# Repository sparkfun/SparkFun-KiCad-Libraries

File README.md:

SparkFun Electronics KiCad Libraries
====================================

This repository contains the SparkFun KiCad Libraries of commonly used parts. It is a cultivated combination of KiCad stock parts,  SparkFun-unique footprints, and open-source 3D models. The main branch is generally proven out but we apologize in advance if these libraries have errors. Please report any issues! We'll fix them quickly.

**Note:** The SparkFun KiCad components contain internal part numbers (**PROD_ID-\***) for ease of manufacture for the SparkFun SMD lines. 

## Theory

KiCad is very good and has a large number of industry specified symbols and footprints. SparkFun has a large number of unique parts and components created since 2002. Rather than converting all previous [SparkFun Eagle libraries](https://github.com/sparkfun/SparkFun-Eagle-Libraries) to KiCad, we are adding new parts to these libraries as we need them for new projects. This gives us the opportunity to clear out old badness, but opens the door to new badness (ie, incorrect footprints) so reader beware!

The SparkFun approach: when a new part needs to be added we decide whether to use a KiCad stock symbol, edit it for use, or create it from scratch. We give preference to the stock KiCad symbol. We give heavy preference to using the original SparkFun footprint, but look at the stock KiCad footprint for inspiration as well. We try to follow the [KiCad Library Conventions](https://klc.kicad.org/) where it makes sense.

Additionally, SparkFun needs to assign various unique manufacturing data (ie, internal part numbers) to parts. To alleviate this, there is a large number of components with an identical symbol each with their own production ID information. For example, capacitors:

We use the following naming conventions to create our 'bubble gum' parts: 

* [capacity]\_[size]\_[voltage]_[tolerance]
* [resistance]\_[size]\_[wattage optional]_[tolerance optional]
* [inductance]\_[size]\_[max current]
* [led color]\_[size]\_[wavelength optional]

## Installing and using these libraries

* [Installing a release via the KiCad PCM](#installing-a-release-via-the-kicad-pcm)
* [Installing a release from zip file - without the PCM_ Library nickname prefix](#installing-a-release-from-zip-file---without-the-pcm_-library-nickname-prefix)
* [Download the current libraries as a zip file](#download-the-current-libraries-as-a-zip-file)
* [Using Git](#using-git)

Internally, these libraries use an Environmental Variable named `SPARKFUN_KICAD_LIBRARY` to reference the footprints and 3D models. This is converted into `KICAD9_3RD_PARTY` during the release process. The release zip file Assets contain `KICAD9_3RD_PARTY` paths. At SparkFun, we use the library as-is with the original `SPARKFUN_KICAD_LIBRARY` environmental variable paths. Our open-source KiCad designs will contain those same environmental variable paths. If you want to be able to _edit_ existing SparkFun schematics and board designs directly, rather than just make use of our components, you need to manually install a true copy or clone of the library. See [Download the current libraries as a zip file](#download-the-current-libraries-as-a-zip-file) and [Using Git](#using-git) below.

### Installing a release via the KiCad PCM

From the fall of 2025, releases of these libraries are available via the KiCad Plugin and Content Manager (PCM).

Open the PCM, select the "Libraries" tab, and type "SparkFun" into the search box. The "Install" button will install the latest release of the libraries.

**If you are using KiCad 10 :** after installing the libraries through the PCM, **close KiCad** and reopen. Only then will the new libraries be visible.

**Note:** this method assumes you have the KiCad Library nickname prefix set to the default of 'PCM_'. If you have cleared the Library nickname prefix, use the [next option](#installing-a-release-from-zip-file---without-the-pcm_-library-nickname-prefix) to install from zip file.

### Installing a release from zip file - without the PCM_ Library nickname prefix

In the KiCad Preferences, you will find settings for "Packages and Updates". The "Library nickname prefix" is applied to any libraries installed through the Plugin and Content Manager (PCM).

If you install these libraries though the PCM, the installation assumes the prefix is 'PCM_'. The symbol footprint names will all be prefixed with 'PCM_'. If you have cleared the prefix, you will need to manually install a different version of the libraries without the footprint prefix:

* Navigate to the libraries [Releases page](https://github.com/sparkfun/SparkFun-KiCad-Libraries/releases)
* You will find two zip file "Assets" attached to each release
* Download the **"without-pcm"** zip file
* In the PCM, use the "Install from File..." option to install the zip file

**If you are using KiCad 10 :** after installing the libraries from file, **close KiCad** and reopen. Only then will the new libraries be visible.

If you are changing the Library prefix to use this installation method, we recommend: clearing the prefix, OK the changes, **close KiCad** and reopen before installing the zip file.

### Download the current libraries as a zip file

Instead of waiting for a release, you can download a copy of the libraries at any time by clicking on the big green `<> Code` button above and selecting the `Download ZIP` option. Or, click on the icon below:

Unzip the file somewhere convenient, usually in `Documents`. If needed, change the folder name from `SparkFun-KiCad-Libraries-main` to `SparkFun-KiCad-Libraries`. Open the KiCad **Symbol Editor** and select `Preferences \ Configure Paths`. Add a new Environmental Variable called `SPARKFUN_KICAD_LIBRARY` and set the Path to the `SparkFun-KiCad-Libraries` folder :

Then select `Preferences \ Manage Symbol Libraries`. Click the folder button to "Add existing library to table". Navigate to the `SparkFun-KiCad-Libraries \ symbols` folder, select all the `SparkFun-.kicad_sym` symbol files and click `Open` :

Then likewise in the **Footprint Editor**, select `Preferences \ Manage Footprint Libraries`. Click the folder button to "Add existing (KiCad folder)". Navigate to the `SparkFun-KiCad-Libraries \ footprints` folder, select everything and click `Select Folder` :

**If you are using KiCad 10 :** after installing the libraries from zip file, **close KiCad** and reopen. Only then will the new libraries be usable.

### Using Git

If you're familiar with GitHub and Git / [GitHub Desktop](https://desktop.github.com/download/), you can stay completely up to date by cloning this repo.

Again, add the Symbols and Footprints Paths as described in the [previous section](#download-the-current-libraries-as-a-zip-file).

If you use the "Watch All Activity" option above, you will be notified each time we Push changes in the libraries. You can then Pull the changes to stay completely up to date. (It's what we do at SparkFun!)

Contents
-------------------

* [/symbols](https://github.com/sparkfun/SparkFun-KiCad-Libraries/tree/main/symbols) -- Schematic symbols
* [/footprints](https://github.com/sparkfun/SparkFun-KiCad-Libraries/tree/main/footprints) -- PCB footprints
* [/3dmodels](https://github.com/sparkfun/SparkFun-KiCad-Libraries/tree/main/3dmodels) -- 3D models - usually in step format

License
-------------------

This libraries are released under the [Creative Commons Attribution 4.0 International](https://creativecommons.org/licenses/by/4.0/) license. 
**You are welcome to use these libraries for commercial purposes.**
For attribution, we ask that when you begin to sell your device using our footprint, you email us with a link to the product being sold. 
We want bragging rights that we helped (in a very small part) to create your 8th world wonder. 
We would like the opportunity to feature your device on our homepage.

Please consider contributing back to these libraries or others to help the open-source hardware community continue to thrive and grow! 

- Your friends at SparkFun

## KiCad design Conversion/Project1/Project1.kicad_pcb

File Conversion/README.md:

Conversion tools and information
====================================

This directory contains information regarding getting the libraries transfered from eagle to kicad.

## Process

This is the evolving breakdown of tasks required to transfer the full set of sparkfun libraries.

* Convert bulk of libraries to Kicad *Manual operation*
  * Use "Out put new part for every foot print type" in lachlanA's ULP
* Use .bat file to run script for all libraries (check paths within)
  * Use custom script to (for each Eagle .lbr):
    * Detag and copy descriptions to .dcm files
    * Add fields for PROD_ID for each KiCad part
    * Add PROD_ID keyword for each part
	  * If not found, apply XXX-00000 for prod id
    * Scrub errant footprint filters by reference Footprint field
    * Report statistics to validate script operation
* Load and save-as for all .mod files to convert to .pretty format. *Manual operation*
* Combine all .mod files to a single .pretty folder. *Manual operation*
  * There will be duplicate file names (should be identical)
  * There will be similar footprint .mod files (should be identical)
* Weed out (about 3) spare F8 commands that were not saved correctly in the lib files (KiCad will tell you they are broken)
* Convert line graphics of .kicad_mod files to poly graphics using other bat
  * Output ends up in Export.pretty
  * When satisfied, overwrite Sparkfun.pretty with contents of Export.pretty

## Notes that led to the above process

### Convert bulk of libraries/boards to Kicad

Use this script for libraries

https://github.com/lachlanA/eagle-to-kicad-libs

Use this script for boards

https://github.com/lachlanA/eagle-to-kicad

**Note:** This is very hacky.  It would be best to establish the proper libraries first, then link to those rather than have the script spit out specific libs for each board.  This insures the resultant file is consistent with the KiCad libraries.

#### Analysis of part naming

In order to write a script, it must link parts from two files.  It seems the only way to do that is by using the name of the component/footprint/etc, so let's explore that.  Using these eagle export scripts, there are a few options for naming convention.

.. But first let's see what happened to a highly nested component in eagle... the 10uF cap.  In eagle, the part is called "10UF" and has sub-parts -0603-... etc for all packages.  In KiCad the symbol is called "10UF" and there are 4 suggested footprints within the footprint filter that are generated, 0603, 0805, 1206, 1210.  This is kind of a problem because I really want to retain a prod_id for each package, so these will need to be un-nested.

To solve this, during library export select the drop down "Combine Parts/package variants where possible" and choose "Out put new part for every foot print type" instead.  The result is that each variant now has it's own (duplicate) symbol.  (note: the filter is still filled with all possible footprints.  **This will need to manualy be fixed**)

For instance, eagle part in file "SparkFun-Capacitors.lbr", the 10UF is:

* "deviceset name="10UF" prefix="C""
  * "device name="-0603-6.3V-20%" package="0603""
  * "device name="-1206-6.3V-20%" package="1206""
  * "device name="-0805-10V-10%" package="0805""
  * "device name="-1210-50V-20%" package="1210""

The resultant parts in KiCad are named:

* 10UF-0603-6.3V-20%
* 10UF-1206-6.3V-20%
* 10UF-0805-10V-10%
* 10UF-1210-50V-20%

.. The superfluous filters are mitigated by a new field "Footprint" which contains "0805", etc.

The conclusion is that the script must identify parts by the part-per-footprint names within the exported libraries for application of prod_id fields.

#### Analysis of library naming

Let's again look at "SparkFun-Capacitors.lbr".  After export, two files are created:

* SparkFun-Capacitors.lib
* SparkFun-Capacitors.mod

When the .lib is re-saved, two files are produced (could be renamed here):

* SparkFun-Capacitors.lib -- library of symbols and fields and stuff
* SparkFun-Capacitors.dcm -- Description and some other stuff

When the .mod is re-saved, a directory is created as such:

* somename.pretty
  * 0402.kicad_mod
  * 0603.kicad_mod
  * 0603-POLAR.kicad_mod
  * ... etc.
  
### Combine footprints and have single source for common footprints

A tool for moving symbols and footprints between .mod and .lib files:

http://www.compuphase.com/electronics/kicadlibrarian_en.htm

### Convert .mod to new format: .pretty (.kicad_mod)

Do this by "saving as" within kicad

### Determine where the descriptions and prod IDs should live

The descriptions are not formatted as well but do show up on the part browser.  The product IDs could be added as keywords (and would be indexed for searching).

A better location for the PROD_IDs would be as a field of the components (probably the symbol).  This can also be edited in the schematic as shown:

With a special BOM plugin, the output CSV contains the extra fields:

File format:

https://en.wikibooks.org/wiki/Kicad/file_formats#Schematic_Libraries_Files_Format

------

*the hardest part of any task is starting*

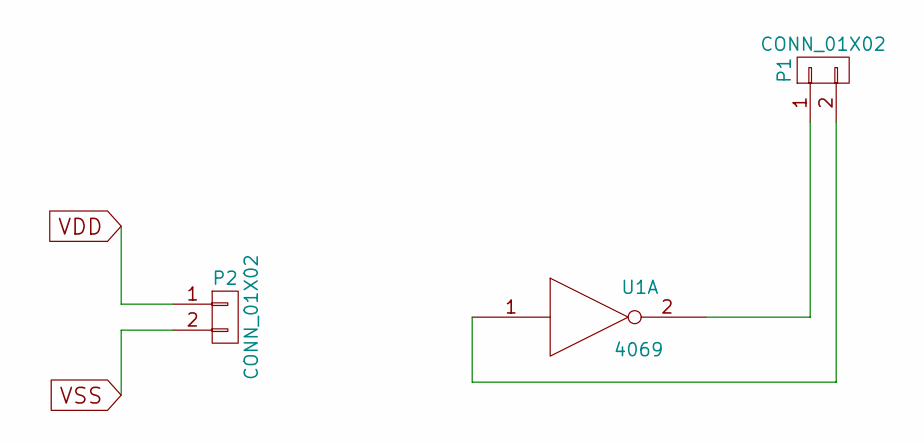
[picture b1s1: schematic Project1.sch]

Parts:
P1, P2: CONN_01X02; Pin_Header_Straight_1x02
U1: 4069; SOIC-14_N

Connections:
unnamed: P1.1, U1.2
unnamed: P1.2, U1.1
VDD: P2.1, U1.14 (VDD)
VSS: P2.2, U1.7 (VSS)

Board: 2 copper layers, 3 parts (0 on the bottom side), 4 nets, no tracks yet.

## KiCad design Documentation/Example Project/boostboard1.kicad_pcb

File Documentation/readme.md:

# Index

### Installation notes

* [InstallationNotes.md](https://github.com/sparkfun/SparkFun-KiCad-Libraries/tree/master/Documentation/InstallationNotes.md) -- Installing KiCad and configuring libraries
* [SparkFunDefaults.md](https://github.com/sparkfun/SparkFun-KiCad-Libraries/tree/master/Documentation/SparkFunDefaults.md) -- Locating and applying our standard UI settings

### Conversion scripts

* [KiCadPadMod.md](https://github.com/sparkfun/SparkFun-KiCad-Libraries/tree/master/Documentation/KiCadPadMod.md) -- Script for modifying footprint pad properties in bulk
* [ScriptConvertSFEEagleLibs.md](https://github.com/sparkfun/SparkFun-KiCad-Libraries/tree/master/Documentation/ScriptConvertSFEEagleLibs.md) -- Notes on using other scripts to do sparkfun-eagle to sparkfun-kicad conversions.

### Usage

* [ProductionOutputs.md](https://github.com/sparkfun/SparkFun-KiCad-Libraries/tree/master/Documentation/ProductionOutputs.md) -- What settings to select when ordering PCBs
* [BOM plugin](https://github.com/sparkfun/SparkFun-KiCad-Libraries/tree/master/Tools/PROD_ID_Bom_Plugin/README.md) -- for outputing PROD_IDs.

### Todo:

* [SparkFunProcess.md](https://github.com/sparkfun/SparkFun-KiCad-Libraries/tree/master/Documentation/SparkFunProcess.md) -- text

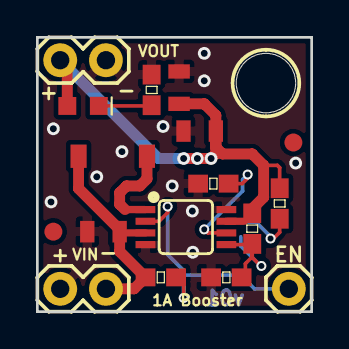
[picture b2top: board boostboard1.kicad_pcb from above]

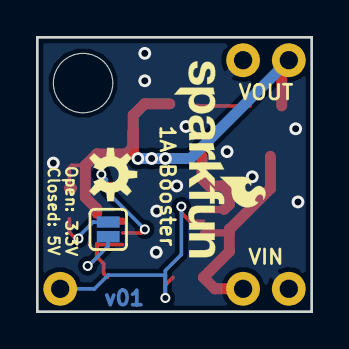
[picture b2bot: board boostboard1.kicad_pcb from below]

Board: 2 copper layers, 15.2 x 15.2 mm, 21 parts (3 on the bottom side), 9 nets.

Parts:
C1, C2, C3: 22UF-0805-6.3V-20%; 0805
D1: LED-RED0603; LED-0603
FD1, FD2: FIDUCIAL1X2; FIDUCIAL-1X2
H1: STAND-OFF
J1, J3: CONN_02; 1X02
J2: CONN_01; 1X01
JP1: JUMPER-SMT_2_NO; SMT-JUMPER_2_NO_SILK
L1: INDUCTOR-CDRH-4.7UH; INDUCTOR_2.2UH
LOGO1: SFE_LOGO_NAME_FLAME.1_INCH; SFE_LOGO_NAME_FLAME_.1
LOGO2: OSHW-LOGOS; OSHW-LOGO-S
R1: 10KOHM-0603-1_10W-1%; 0603
R2, R4: 100KOHM-0603-1_10W-1%; 0603
R3, R5: 820KOHM-0603-1_10W-1%; 0603
R6: 4.7KOHM-0603-1_10W-1%; 0603
U1: PAM2401; MSOP8

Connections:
/EN: J2.1, R1.2, U1.2
/FB: JP1.2, R3.1, R4.2, U1.5
/GND: C1.2, C2.2, C3.2, J1.1, J3.1, R2.2, R4.1, R6.1, U1.4, U1.8
/LX: L1.P$2, U1.1
/RSET: R2.1, U1.6
/VBATT: C1.1, J1.2, L1.P$1, R1.1, U1.3
/VCC: C2.1, C3.1, D1.A, J3.2, R3.2, R5.2, U1.7
unnamed: D1.C, R6.2
unnamed: JP1.1, R5.1

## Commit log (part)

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2025-07-23 Add CD74HC4067
2025-07-23 Update USB C connector to v9
2025-07-23 Add 2x3 2mm connector
2025-08-12 Moves the Outline of the screen down to more correctly represent its position relative to the fold
2025-08-15 Adding finger sensor
2025-08-15 Add 8mm SMA connector.
2025-08-18 Add 3D models for RF filter and IMU sensor components
    Added STEP files for RFCMF1220100M4T filter and IM19 IMU
    - RFCMF1220100M4T used on Flex Breakout
    - IM19 used on various GNSS tilt-compensation boards
2025-08-19 Add 9 pin castellated connector
2025-08-19 Fix value on SMD battery
2025-08-19 Add search keywords to 1nF and 1uF cap. Add 0402 DNP cap.
2025-08-19 Add CH340E
2025-08-19 Add 9.1nH inductor
2025-08-19 Add DFN and Filter package and step. Add SAW filter and LNA.
2025-08-19 Add search keywords to LG290P
2025-08-19 Add ceramic GNSS antenna
2025-08-19 Add search term
2025-08-19 Fix FP. Still needs to be moved into lib.
2025-08-19 Add QFN-16 EP 1.7mm FP
2025-08-21 Adds a Ethernet transformer and SMD RJ45 connector
2025-08-21 Update castellated pads to remove DRC errors
2025-08-22 Adds 2x3 2mm pitched smd connector, updates rj45 connector
2025-08-22 Updates pin one indicators on mag and connector, removes ground pour from top layer
    * Reduces the size of the keepout area slightly
2025-08-22 Adds PROD_ID to all parts
2025-08-22 Changes mechanical shield pins to be through hole components with paste
2025-08-25 Adds 10% overpaste for RJ45 shield pings
2025-08-25 Adds 3D models for 2x3 smd part, RJ45 Recessed, and Transformer, increase silk on Transformer silk
2025-08-26 Changes 536k resistor to a 549k resistor
2025-08-27 Add IM19
2025-08-27 adds route out to b.fab on RJ45
2025-08-27 Add parts for Red Vision XRP kit
2025-08-27 Add remaining Red Vision XRP parts
2025-08-27 Add 2x10_SMD_RA 3D model
    Also fix model path for corresponding footprint
2025-08-28 Replace 3D model for RFCMF1220100M4T - see #211
2025-08-28 Revert "Add 3D models for RF filter and IMU sensor components"
    This reverts commit 769dfc580286080621b0bb5c429cb8d5502734f7.
2025-08-28 Tweak 21-pin FPC connector
2025-08-29 Add LS550G and LC762Z. Update part IDs.
2025-08-29 Update crystal FP name to match.
2025-08-29 Rename camera connector
2025-08-29 Add keywords/datasheet to connector
2025-08-29 Fix FPC connector name and FP
2025-08-29 Fix display name and FP
2025-08-29 Move camera connector to camera folder
2025-08-29 Fix 3D model names
2025-08-29 Add datasheet
2025-08-29 Rename USB choke
2025-08-29 Fix FP name on sym
2025-08-29 Move LNA to IC folder. Add PROD_ID to GNSS antenna.
2025-08-29 Move DFN-6 FP to standard folder
2025-08-29 Separate I2C and analog pins of R3 shield
2025-08-29 Add Red Vision logo
2025-08-29 Add 2x10 0.1in vertical SMD header
2025-08-29 Fix 2x20 header pin order to zig-zag
2025-09-02 Add SAM-M8Q
2025-09-02 Change name to socket, move pin 1 to upper right on symbol and FP, align 3D model.
2025-09-03 Add pitches and orientations to connector symbol and FP names
2025-09-05 Add pitch values
2025-09-05 Decrease paste on USB C
2025-09-09 Increase the post standoff sizes for both parts
2025-09-09 Add electrically connected standoff
2025-09-09 Update SAM-M8Q model
2025-09-09 Update SAM-M8Q FP name
2025-09-10 Add mosaic-G5
2025-09-10 Fix RFCMF1220100M4T symbol pin numbers
    Changing to the 'small' symbol revealed this error. See commit 1eb09a11334eea2e0cd8110439974932e5bae5d8
2025-09-10 Add 0.85V power symbol
2025-09-10 Add 'Septentrio' to FP and model names. Colorize 3D model.
2025-09-12 Add SMD super cap
2025-09-12 Rename GPS folders to GNSS
2025-09-12 Add LG580P
2025-09-12 Add DAN-F10N
2025-09-13 Add pin 1 indicator to super cap
2025-09-13 Convert CP pads to GND on LS5x FP
2025-09-13 Update resistors to use new/cheaper resistors
2025-09-17 Update footprint for LG580P
    Updated pad position
    Updated 3D model position
2025-09-20 Update README - add installing and using
2025-09-23 Fix rogue SPARKFUN_3DMODEL_DIR
2025-09-23 Add L829-1J1T-43 MagJack model - remove KIPRJMOD
2025-09-23 Add MPM3630.STEP - remove KIPRJMOD path
2025-09-23 Add PROD_ID
2025-09-23 Add Yellow 0402 LED
2025-09-23 Add AP3429 Buck
2025-09-23 Move VCC_RF pins on LS550
2025-09-23 Update description on supercap
2025-09-23 Adding two ferrite beads. Updating PROD_IDs to use preferred stock.
2025-09-23 Add 'Ferrite' in front of ferrites.
2025-09-23 Fix inductor symbols
2025-09-23 Remove old symbols
2025-09-24 Add VCNL4040
2025-09-26 Resets branch and re-adds connector symbols and footprints
2025-09-26 Re-adds the B10601S
2025-09-26 Re-adds 75 Ohm resistor
2025-09-26 Change linked KiCad models to local copies
2025-09-26 Adds 3d models for transformer, and 2x03 smd connector
2025-09-26 Rotates 3d model of B10601S
2025-09-26 Change linked KiCad 3D models to local copies
2025-09-26 Change 2x03 connector names
2025-09-26 Rename RJ45 connector. Add model.
2025-09-26 Modify resistor symbol to match
2025-09-26 Fix typo
2025-09-26 Revert "Ethernet parts"
2025-09-29 Adds ethernet parts
2025-10-01 Adds the HMC6343
2025-10-01 Moves the footprint to SparkFun-Sensors
2025-10-01 Slighty adjusts the symbol
2025-10-02 Adds 3D model and shrinks the symbol
2025-10-03 Fixes pin numbers on symbol
2025-10-03 Updates symbol according to newer datasheet
2025-10-16 PCM updates : rename folders - step 1
2025-10-16 PCM updates : rename folders - step 2
2025-10-16 PCM updates : move 3dmodels
2025-10-16 PCM updates : update 3dmodels paths
2025-10-16 Add build and workflow
2025-10-16 Update README and metadata
2025-10-17 Move 3D models into correct sub folders
2025-10-17 Update model paths
2025-10-17 Delete FreeCAD 5mm LED models
    Unused
    It looks like this became: LED_PTH_5mm_Red.step
2025-10-17 Decapitalization - step 1
2025-10-17 Decapitalization - step 2
2025-10-17 Decapitalization - step 3
2025-10-20 Update README. Add extra screenshots
2025-10-21 Add Download Zip
2025-10-30 Adds the 2x03 SMD Connector, RJ45 Mid Mount, Ethernet Transformer, Digital Compass
2025-11-08 Add models for Pro Mini, PTH resistors, TO-220
2025-11-08 Update footprints
2025-11-08 Add pin numbers to JST 2 pin. Add PTH trim pot and resistor. Add PTH MOSFET. Add Pro Mini.
2025-11-08 Adjust FP to use new model
2025-11-08 Rename RJ45 connectors to follow nomenclature
2025-11-08 Add SparkFun to keywords
2025-11-08 Show REF on FP
2025-11-08 Add missing NC pins to LIS3DH
2025-11-11 Update LED naming conventions
2025-11-25 Update 1x06 SMD Socket
    Update schematic symbol
    - Fix description to "female" pins
    - Update datasheet link
    - Update part number (for internal use)
    Add 3D model for footprint
    Links 3D model to the footprint of the schematic symbol
2025-12-01 Add 619k, 430k resistors.
2025-12-01 Add TLV75733PDRV and TPL730AD regulator.
2025-12-01 Add power symbols for SD control
2025-12-01 Add PCA9536 4bit I2C expander.
2025-12-01 Remove TLV75733 (moved to Regulator folder)
2025-12-01 Reorder pins on MIMXRT1062. Add all balls.
2025-12-01 Bring SOT-886 into library.
2025-12-01 Update crystal footprint to v9 KiCad
2025-12-01 Remove castellated property from SMD pads
2025-12-01 Add hyperRAM and octal flash
2025-12-01 Touchup microSD FP
2025-12-04 Add symbol for CAP1203
2025-12-05 Fix PTH Test Point
    Update footprint
2025-12-05 Add SMD relay
2025-12-05 Update cap FP to v9
2025-12-05 Remove silk from TVS FP
2025-12-05 Expose slight annular ring on bottom layer of castellated connector
2025-12-05 Fix fill color of CAP1203
2025-12-05 Add PROD_IDs
2025-12-06 fix: unshrouded cortex debug connector footprint
    The SparkFun-Connector:Debug-Cortex-2x5_P1.127mm-SMD-Unshrouded is
    not correctly linked to the corresponding footprint.
2025-12-08 Add NC pins to Xtal
2025-12-08 Fix ERC power warnings on symbols
2025-12-08 Add 4.2x3.2mm tactile switch color variant
2025-12-08 Add SMD to relay name
2025-12-11 Add initial symbol for CY8CMBR3102 capacitive touch sensor
2025-12-12 Update CY8CMBR3 symbol size and fill
2025-12-12 Add initial symbol for 0603 560ohm resistor
2025-12-12 Hide pin names for 560ohm 0603 resistor
2025-12-12 Add 0603 2200pF X7R capacitor symbol
2025-12-14 fix: ws2812_5050 footprint
    The SparkFun-LED:WS2812B_5050 does not link to the correct footprint.
2025-12-16 Add PROD_ID for new capacitor, resistor and IC
2025-12-16 Round inner pads
2025-12-16 Update FPs to v9
2025-12-16 Add TLV70018 regulator
2025-12-17 Fix 2200pF capacitor part number and datasheet
2025-12-17 Resize CY8CMBR3102 symbol
2026-01-07 Update name of SMD diode.
2026-01-07 Add MX25UW12845G.
2026-01-07 Adjust pin arrangement on MIMXRT1062
2026-01-07 Add TCA9555RTWR GPIO expander
2026-01-13 Add ESP32-C5-WROOM-1
2026-01-13 Update notes on ESP32-C5 GPIO in symbol
2026-01-13 Add datasheet link
2026-01-13 Add PROD_ID to ESP32-C5 symbols
2026-01-21 Fixes prod-id for the 3.3uH inductor
2026-01-21 Add 40MHz crystal
2026-01-23 Update SOD-523 FP to match KiCad built-in
    For better attachment to paste during placement.
2026-01-23 Add Teensy 4.1 shield board outline
2026-01-23 Add 16V TVS
2026-01-23 Add MCP2558
2026-01-23 Add JW5026
2026-01-23 Add CMT8021
2026-01-23 Fix stacked power pins
2026-01-23 Add Teensy 4.1 board outline FP
2026-01-23 Move pin one indicator
2026-01-23 Add 24MHz 3.2x2.5mm
2026-01-23 Update PROD_ID
2026-01-26 Add 5mm LEDs. Add 7-segment displays.
2026-01-26 Update SOT23-3, SOT-363, add SOT-353 FP.
2026-01-27 Add 1x08, 1x10 LIF 1mm connectors
2026-01-27 Add green 5mm LED
2026-01-27 Add initial symbol and footprint for AS7331
2026-01-27 Align pins to grid
2026-01-27 Add already-stocked 3.3M resistor
2026-01-27 Misc fixes for as7331
2026-01-28 added 3d part and footprint
2026-01-28 Add NC pads to avoid ERC warnings.
2026-01-28 Add symbol and datasheet
2026-01-28 Add 4.02k 0402 resistor
2026-02-04 Update 3d models for new parts
2026-02-05 Adjust FP on QFN-24 to known good values
2026-02-05 Add XDFN4 FP for TLC77201
2026-02-05 Add VSD_IO power symbol
2026-02-05 Change CH213 to K variant
2026-02-05 Add 806k 0402
2026-02-05 Fix 404 for locking FP and symbols
    Fix #249
2026-02-05 Add symbols and footprints for new UV/IR LEDs
2026-02-05 Fix symbols using SOT-363 after footprint rename
    Fixes #256
2026-02-05 Add PROD_IDs for new sparkle parts
2026-02-05 Update AS7331 schematic to include other VSSA pins
2026-02-05 Add ground tie symbol and footprint
2026-02-05 Fix for new jumper
2026-02-13 Add polarity markings to relay
2026-02-13 Change stacked hidden power pins to passive
2026-02-13 Update footprint link
2026-02-26 Add P23M
2026-02-27 Add IM23
2026-02-27 Add M1.6 screw
2026-03-02 Add P23M.
2026-03-02 Correct Z location on IM23.
2026-03-04 Adds two new resistors and high side switch IC
2026-03-05 Adds PTC
2026-03-10 Adds new switch, capacitor, and fuse
2026-03-24 Fixes pins on Teensy board symbol
2026-03-24 Updates fuse
2026-03-24 Adds PROD_ID to fuse
2026-03-30 Add 74HC4066 TSSOP variant
2026-03-30 Exclude DNP parts from BOM and output files
2026-03-30 Add TSSOP-14 model
2026-03-30 Name mount pads on connector
2026-03-30 Tighten courtyard on locking JSTs
2026-03-30 Update P23M model
2026-03-30 Adds PROD_ID
2026-03-30 Updates 4.7nF Capacitor
2026-03-30 Fixes missing pin
2026-03-30 Adds PROD_ID to amplifier
2026-04-01 Add PROD_ID CH213K and TLV77201
2026-04-10 Push w/ misc updates before leaving
2026-04-14 Update 74LVC1G175 footprint
2026-04-20 Add ESP32-C6-Mini-1
2026-04-28 Added STEP file
2026-05-08 Adds new parts for ADE7953 Current Sensor
    - ADE7953
    - 5.6 Ohm (high-precision) 0603
    - 3.579MHz XTAL Oscillator
2026-05-12 Add MicroMod library
2026-05-16 swap margin for f.courtyard
2026-05-21 Add missing 3D model to 0806 coil footprint
2026-05-28 Adding parts for Facet FP e-Paper display
2026-06-10 Fixes model
2026-06-10 Add NX3008NBKW
2026-06-10 Add ZED-X20D
2026-06-13 downgrade to kicad 9
2026-06-17 Move User.1 (Milling) to F.Fab or User.2
2026-06-17 Rasp Pi User.1 changes
2026-06-22 Added new components from Qwiic Boards
    - ADE7953ACPZ
    - 3.759MHz Oscillator
    - INA2XX
    - RT9080N-08GJ5
    - MCP3221
    - ADC101C
2026-06-24 Updated BMI330 IMU PROD-ID
